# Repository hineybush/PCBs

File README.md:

# PCBs
A small collection of PCBs I've made in KiCad and that I feel are ready to be released.

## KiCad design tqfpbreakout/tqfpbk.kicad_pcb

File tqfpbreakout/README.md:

#TQFP IC breakout board
# ** NOT FINISHED **

This is a super basic breakout based on a 14mm-pitch TQFR IC footprint. It is designed to use 4 16-pin headers. All pins are numbered on the bottom side, and the outermost corner pins are numbered on the topside.

The TQFP footprint can be found in my fork of [The Keebrary](https://github.com/hineybush/TheKeebrary.pretty), the header footprint is from the default KiCad Pin Headers library.

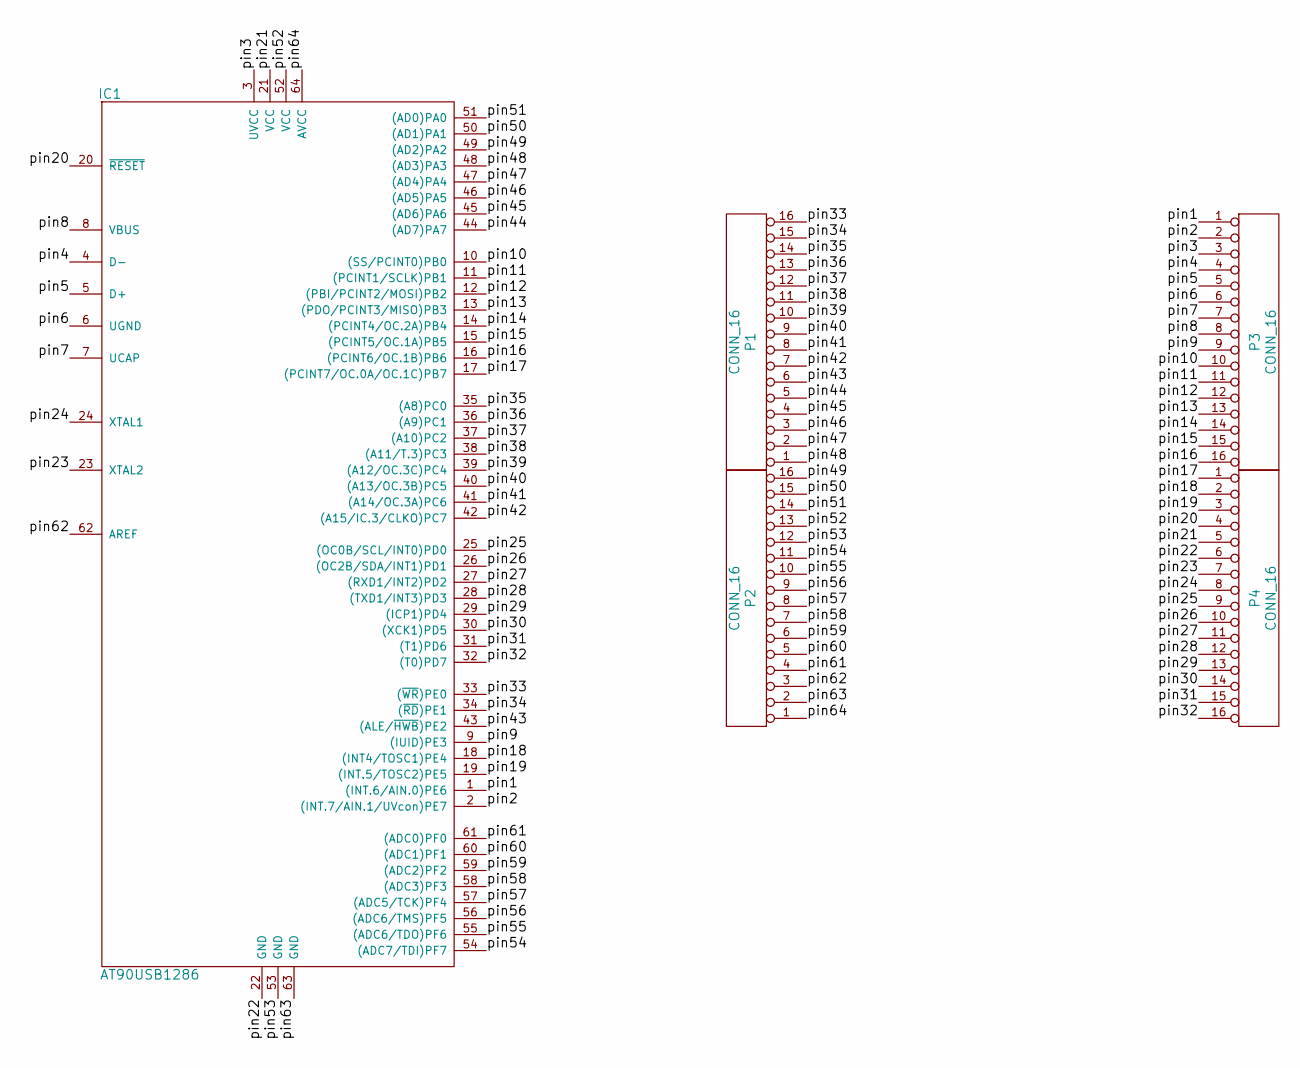
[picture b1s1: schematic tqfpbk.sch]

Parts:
IC1: AT90USB1286; AT90USB1286_TQFP_14mm
P1, P2, P3, P4: CONN_16; Pin_Header_Straight_1x16

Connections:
/pin1: IC1.1 ((INT.6/AIN.0)PE6), P3.1
/pin2: IC1.2 ((INT.7/AIN.1/UVcon)PE7), P3.2
/pin3: IC1.3 (UVCC), P3.3
/pin4: IC1.4 (D-), P3.4
/pin5: IC1.5 (D+), P3.5
/pin6: IC1.6 (UGND), P3.6
/pin7: IC1.7 (UCAP), P3.7
/pin8: IC1.8 (VBUS), P3.8
/pin9: IC1.9 ((IUID)PE3), P3.9
/pin10: IC1.10 ((SS/PCINT0)PB0), P3.10
/pin11: IC1.11 ((PCINT1/SCLK)PB1), P3.11
/pin12: IC1.12 ((PBI/PCINT2/MOSI)PB2), P3.12
/pin13: IC1.13 ((PDO/PCINT3/MISO)PB3), P3.13
/pin14: IC1.14 ((PCINT4/OC.2A)PB4), P3.14
/pin15: IC1.15 ((PCINT5/OC.1A)PB5), P3.15
/pin16: IC1.16 ((PCINT6/OC.1B)PB6), P3.16
/pin17: IC1.17 ((PCINT7/OC.0A/OC.1C)PB7), P4.1
/pin18: IC1.18 ((INT4/TOSC1)PE4), P4.2
/pin19: IC1.19 ((INT.5/TOSC2)PE5), P4.3
/pin20: IC1.20 (~RESET), P4.4
/pin21: IC1.21 (VCC), P4.5
/pin22: IC1.22 (GND), P4.6
/pin23: IC1.23 (XTAL2), P4.7
/pin24: IC1.24 (XTAL1), P4.8
/pin25: IC1.25 ((OC0B/SCL/INT0)PD0), P4.9
/pin26: IC1.26 ((OC2B/SDA/INT1)PD1), P4.10
/pin27: IC1.27 ((RXD1/INT2)PD2), P4.11
/pin28: IC1.28 ((TXD1/INT3)PD3), P4.12
/pin29: IC1.29 ((ICP1)PD4), P4.13
/pin30: IC1.30 ((XCK1)PD5), P4.14
/pin31: IC1.31 ((T1)PD6), P4.15
/pin32: IC1.32 ((T0)PD7), P4.16
/pin33: IC1.33 ((~WR~)PE0), P1.16
/pin34: IC1.34 ((~RD~)PE1), P1.15
/pin35: IC1.35 ((A8)PC0), P1.14
/pin36: IC1.36 ((A9)PC1), P1.13
/pin37: IC1.37 ((A10)PC2), P1.12
/pin38: IC1.38 ((A11/T.3)PC3), P1.11
/pin39: IC1.39 ((A12/OC.3C)PC4), P1.10
/pin40: IC1.40 ((A13/OC.3B)PC5), P1.9
/pin41: IC1.41 ((A14/OC.3A)PC6), P1.8
/pin42: IC1.42 ((A15/IC.3/CLKO)PC7), P1.7
/pin43: IC1.43 ((ALE/~HWB~)PE2), P1.6
/pin44: IC1.44 ((AD7)PA7), P1.5
/pin45: IC1.45 ((AD6)PA6), P1.4
/pin46: IC1.46 ((AD5)PA5), P1.3
/pin47: IC1.47 ((AD4)PA4), P1.2
/pin48: IC1.48 ((AD3)PA3), P1.1
/pin49: IC1.49 ((AD2)PA2), P2.16
/pin50: IC1.50 ((AD1)PA1), P2.15
/pin51: IC1.51 ((AD0)PA0), P2.14
/pin52: IC1.52 (VCC), P2.13
/pin53: IC1.53 (GND), P2.12
/pin54: IC1.54 ((ADC7/TDI)PF7), P2.11
/pin55: IC1.55 ((ADC6/TDO)PF6), P2.10
/pin56: IC1.56 ((ADC6/TMS)PF5), P2.9
/pin57: IC1.57 ((ADC5/TCK)PF4), P2.8
/pin58: IC1.58 ((ADC3)PF3), P2.7
/pin59: IC1.59 ((ADC2)PF2), P2.6
/pin60: IC1.60 ((ADC1)PF1), P2.5
/pin61: IC1.61 ((ADC0)PF0), P2.4
/pin62: IC1.62 (AREF), P2.3
/pin63: IC1.63 (GND), P2.2
/pin64: IC1.64 (AVCC), P2.1

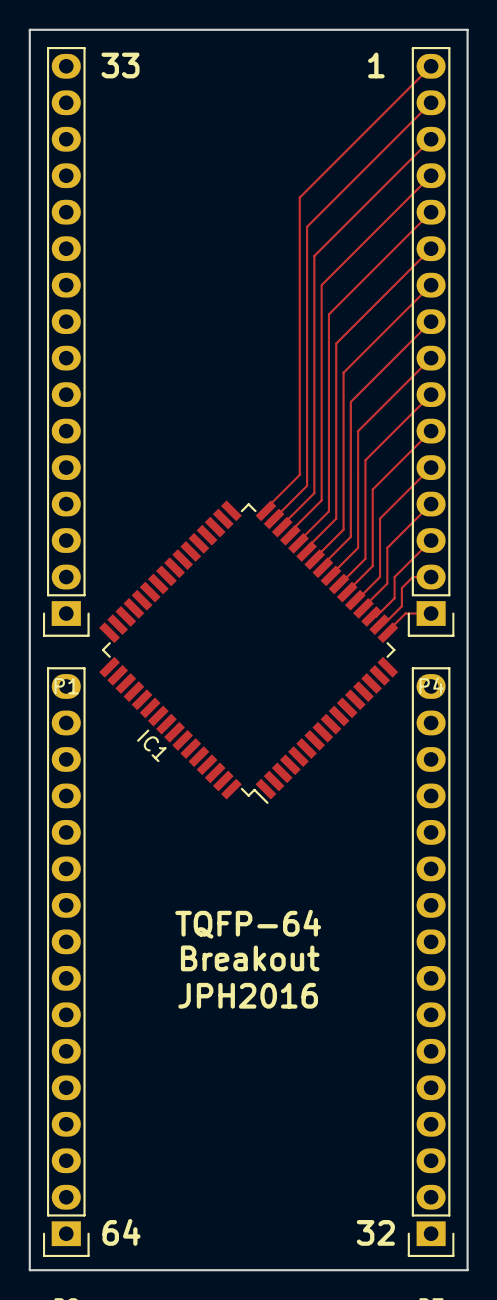
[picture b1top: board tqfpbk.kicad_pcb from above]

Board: 2 copper layers, 30.5 x 86.4 mm, 5 parts (0 on the bottom side), 64 nets.
